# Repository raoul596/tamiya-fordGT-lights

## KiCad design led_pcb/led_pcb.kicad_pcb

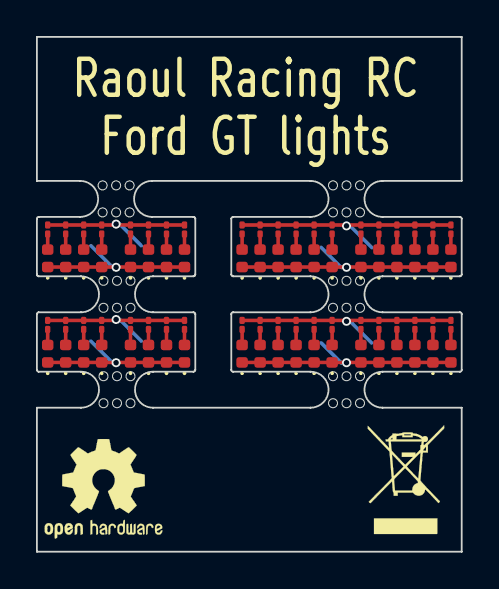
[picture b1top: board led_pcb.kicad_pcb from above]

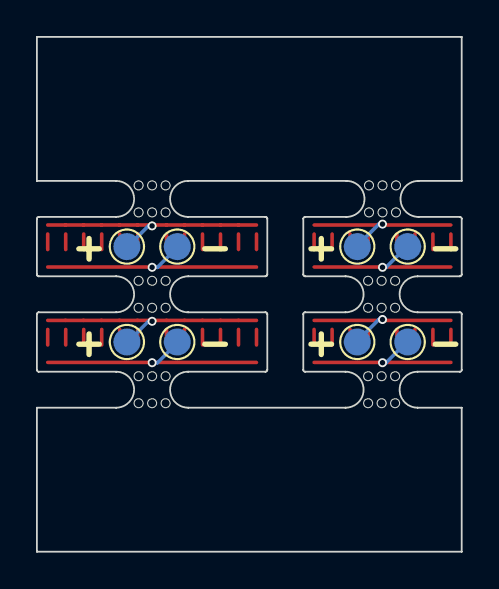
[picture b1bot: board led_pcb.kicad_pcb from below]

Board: 2 copper layers, 23.6 x 28.6 mm, 94 parts (8 on the bottom side), 24 nets.

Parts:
D1, D2, D3, D4, D5, D6, D7, D8, D9, D10, D11, D12, D13, D14, D15, D16, D17, D18, D19, D20, D21, D22, D23, D24, D25, D26, D27, D28, D29, D30, D31, D32, D33, D34, D35, D36, D37, D38, D39, D40: LED; LED_0402_1005Metric
R1, R2, R3, R4, R5, R6, R7, R8, R9, R10, R11, R12, R13, R14, R15, R16, R17, R18, R19, R20, R21, R22, R23, R24, R25, R26, R27, R28, R29, R30, R31, R32, R33, R34, R35, R36, R37, R38, R39, R40: R; R_01005_0402Metric
TP1, TP3, TP5, TP7: VCC; TestPoint_Pad_D1.5mm
TP2, TP4, TP6, TP8: GND; TestPoint_Pad_D1.5mm
mouse-bite-2mm-slot, mouse-bite-2mm-slot#2, mouse-bite-2mm-slot#3, mouse-bite-2mm-slot#4, mouse-bite-2mm-slot#5, mouse-bite-2mm-slot#6: VAL**; mouse-bite-2mm-slot

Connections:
GND: D1.1 (K), D2.1 (K), D3.1 (K), D4.1 (K), D5.1 (K), D6.1 (K), D7.1 (K), D8.1 (K), D33.1 (K), D34.1 (K), D35.1 (K), D36.1 (K), D37.1 (K), D38.1 (K), D39.1 (K), D40.1 (K), TP2.1, TP8.1
GND1: D9.1 (K), D10.1 (K), D11.1 (K), D12.1 (K), D13.1 (K), D14.1 (K), D15.1 (K), D16.1 (K), D17.1 (K), D18.1 (K), D19.1 (K), D20.1 (K), D21.1 (K), D22.1 (K), D23.1 (K), D24.1 (K), D25.1 (K), D26.1 (K), D27.1 (K), D28.1 (K), D29.1 (K), D30.1 (K), D31.1 (K), D32.1 (K), TP4.1, TP6.1
unnamed: D1.2 (A), D33.2 (A), R1.2, R33.2
unnamed: D2.2 (A), D34.2 (A), R2.2, R34.2
unnamed: D3.2 (A), D35.2 (A), R3.2, R35.2
unnamed: D4.2 (A), D36.2 (A), R4.2, R36.2
unnamed: D5.2 (A), D37.2 (A), R5.2, R37.2
unnamed: D6.2 (A), D38.2 (A), R6.2, R38.2
unnamed: D7.2 (A), D39.2 (A), R7.2, R39.2
unnamed: D8.2 (A), D40.2 (A), R8.2, R40.2
unnamed: D9.2 (A), D21.2 (A), R9.2, R21.2
unnamed: D10.2 (A), D22.2 (A), R10.2, R22.2
unnamed: D11.2 (A), D23.2 (A), R11.2, R23.2
unnamed: D12.2 (A), D24.2 (A), R12.2, R24.2
unnamed: D13.2 (A), D25.2 (A), R13.2, R25.2
unnamed: D14.2 (A), D26.2 (A), R14.2, R26.2
unnamed: D15.2 (A), D27.2 (A), R15.2, R27.2
unnamed: D16.2 (A), D28.2 (A), R16.2, R28.2
unnamed: D17.2 (A), D29.2 (A), R17.2, R29.2
unnamed: D18.2 (A), D30.2 (A), R18.2, R30.2
unnamed: D19.2 (A), D31.2 (A), R19.2, R31.2
unnamed: D20.2 (A), D32.2 (A), R20.2, R32.2
VCC: R1.1, R2.1, R3.1, R4.1, R5.1, R6.1, R7.1, R8.1, R33.1, R34.1, R35.1, R36.1, R37.1, R38.1, R39.1, R40.1, TP1.1, TP7.1
VCCQ: R9.1, R10.1, R11.1, R12.1, R13.1, R14.1, R15.1, R16.1, R17.1, R18.1, R19.1, R20.1, R21.1, R22.1, R23.1, R24.1, R25.1, R26.1, R27.1, R28.1, R29.1, R30.1, R31.1, R32.1, TP3.1, TP5.1

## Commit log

2022-10-28 Firts version of low and high beam lights
